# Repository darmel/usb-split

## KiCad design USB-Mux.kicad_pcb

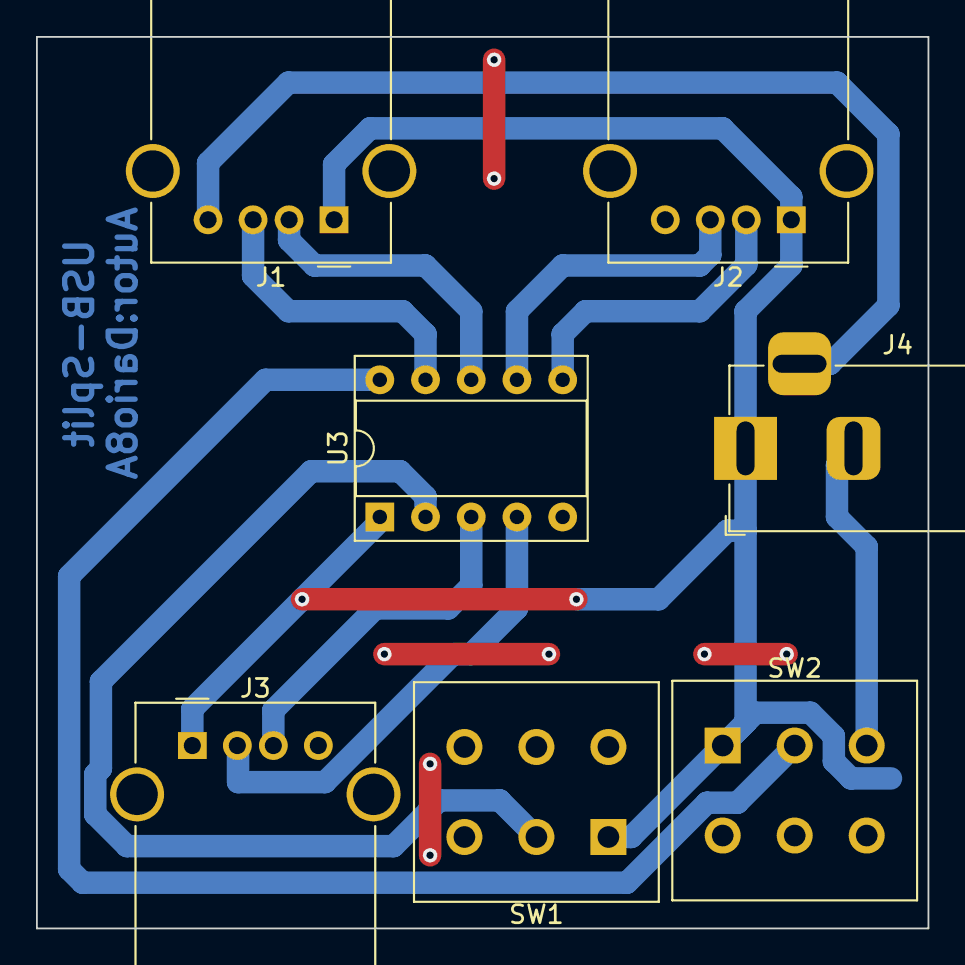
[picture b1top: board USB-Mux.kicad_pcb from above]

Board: 2 copper layers, 49.5 x 49.5 mm, 7 parts (0 on the bottom side), 10 nets.

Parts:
J1, J2, J3: USB_A; USB_A_Molex_67643_Horizontal
J4: Barrel_Jack_Switch; BarrelJack_Horizontal
SW1, SW2: SW_Push_DPDT; SW_PUSH_E-Switch_FS5700DP_DPDT
U3: FSUSB42MUX; DIP-10_W7.62mm_Socket

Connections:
Earth: J1.4, J2.4, J3.4, J4.2, J4.3, SW1.3, SW2.3, U3.5
unnamed: J1.2, U3.8
unnamed: J1.3, U3.9
unnamed: J2.2, U3.6
unnamed: J2.3, U3.7
unnamed: J3.2, U3.4
unnamed: J3.3, U3.3
unnamed: SW1.2, U3.2
unnamed: SW2.2, U3.10
VDD: J1.1, J2.1, J3.1, J4.1, SW1.1, SW2.1, U3.1

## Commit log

2020-10-28 sub split v01
